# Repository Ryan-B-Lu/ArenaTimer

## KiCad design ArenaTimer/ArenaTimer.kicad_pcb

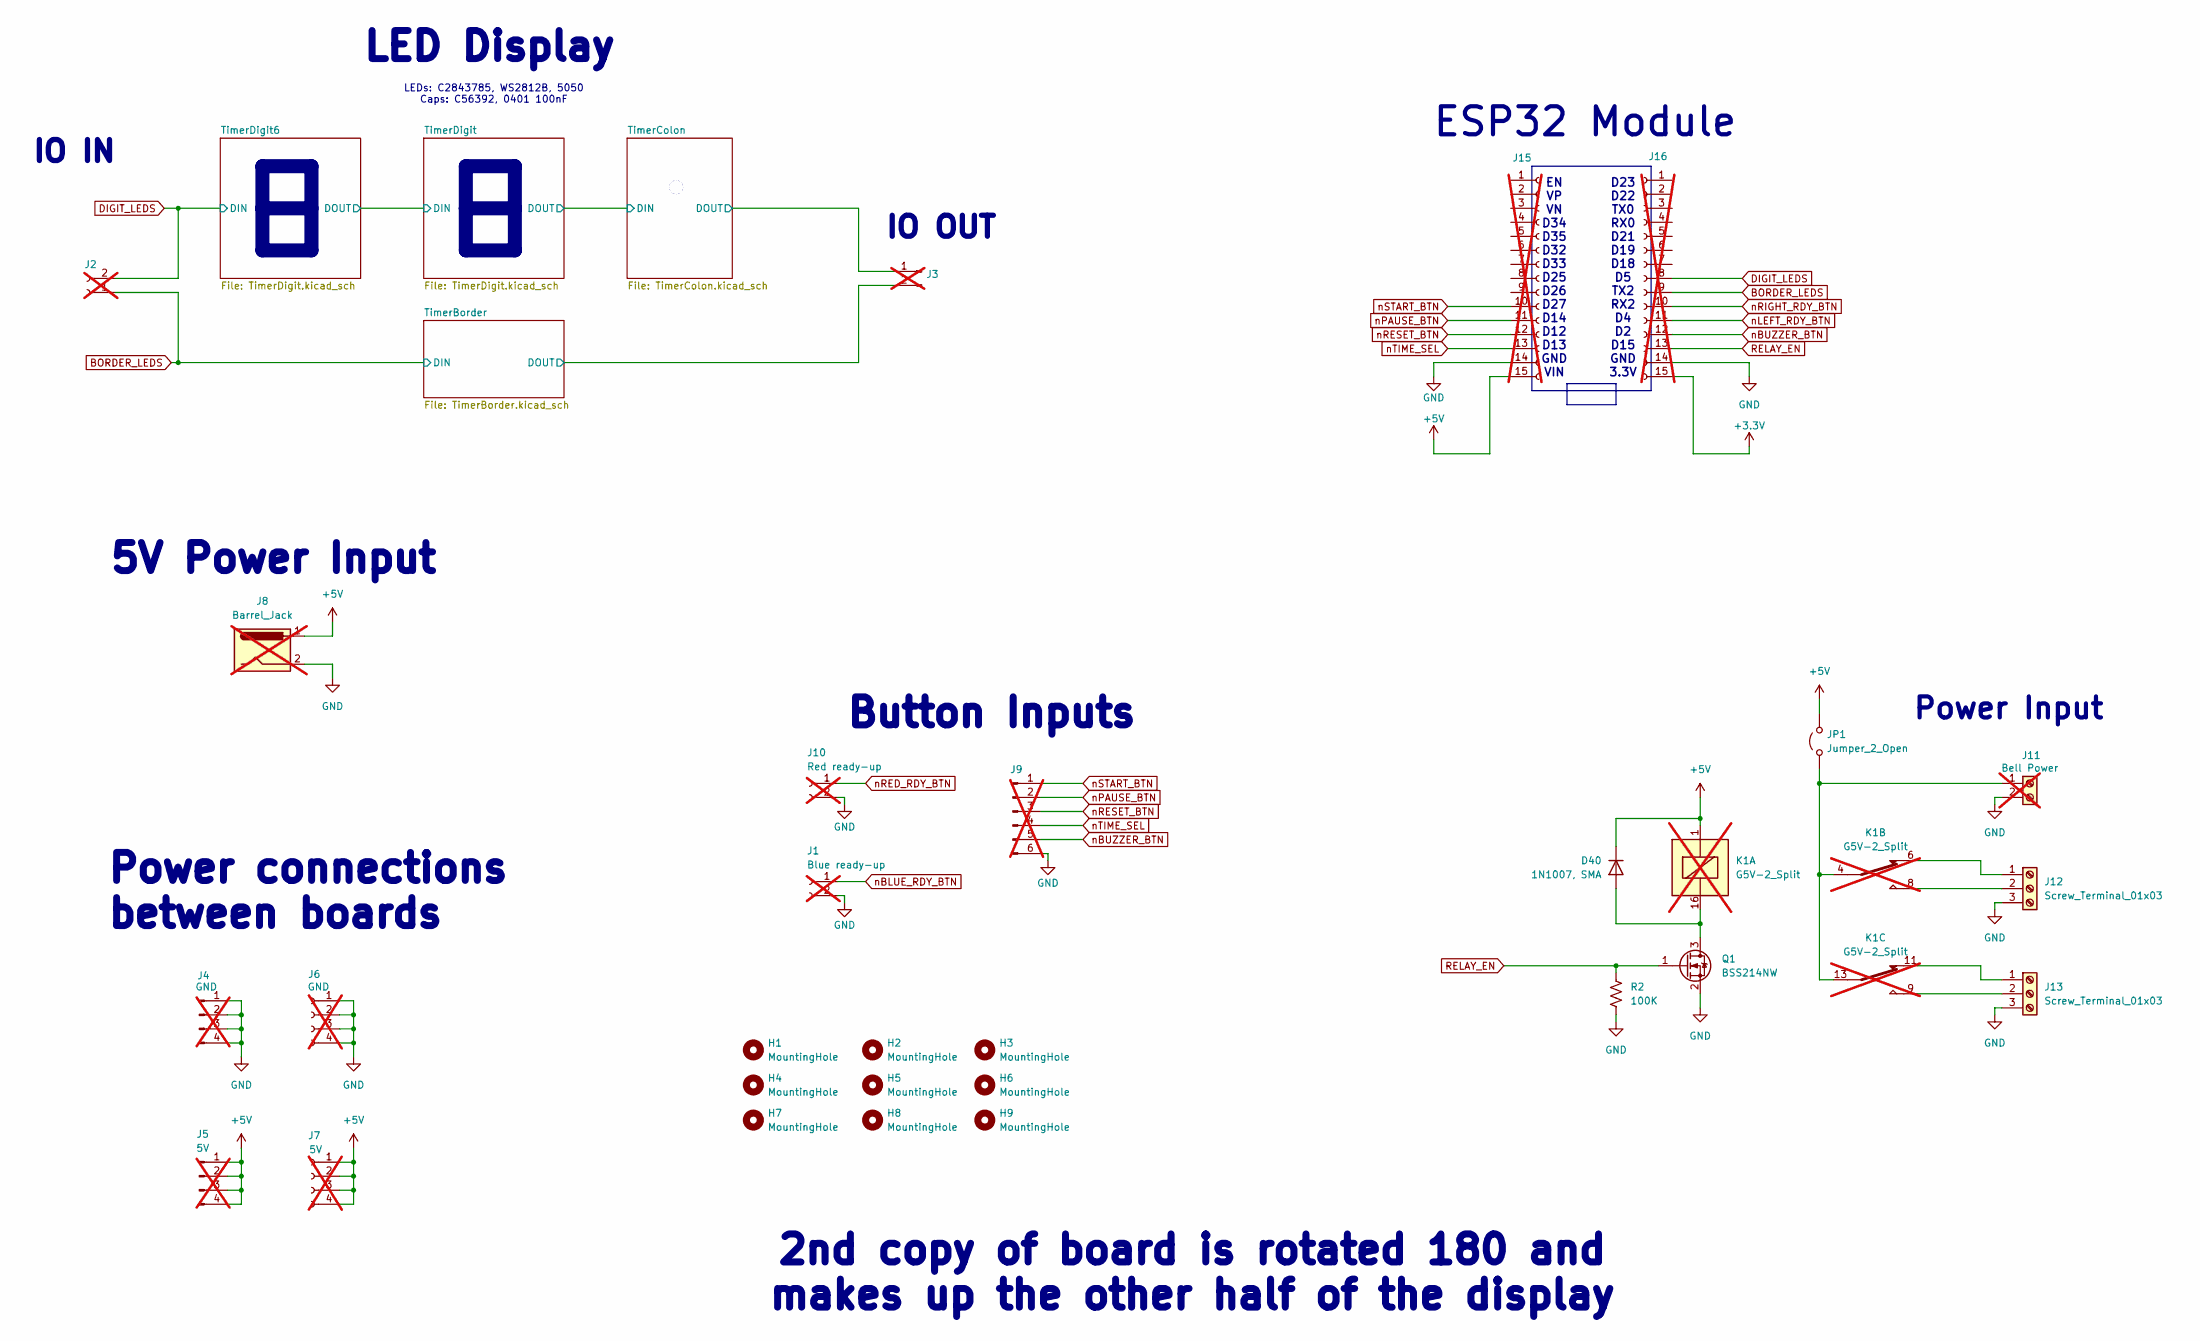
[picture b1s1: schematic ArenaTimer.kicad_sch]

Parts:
D40: 1N1007, SMA; D_SMA; LCSC C727081
H1, H2, H3, H4, H5, H6, H7, H8, H9: MountingHole; MountingHole_3.2mm_M3
J1: Blue ready-up; JST_EH_S2B-EH_1x02_P2.50mm_Horizontal; LCSC C19271377; not fitted
J2: Conn_01x02_Socket; PinSocket_1x02_P2.54mm_Horizontal; not fitted
J3: Conn_01x02_Pin; PinHeader_1x02_P2.54mm_Horizontal; not fitted
J4: GND; PinHeader_1x04_P2.54mm_Horizontal; not fitted
J5: 5V; PinHeader_1x04_P2.54mm_Horizontal; not fitted
J6: GND; PinSocket_1x04_P2.54mm_Horizontal; LCSC C5142237; not fitted
J7: 5V; PinSocket_1x04_P2.54mm_Horizontal; LCSC C5142237; not fitted
J8: Barrel_Jack; BarrelJack_Horizontal; LCSC C381115; not fitted
J9: Conn_01x06_Pin; JST_EH_S6B-EH_1x06_P2.50mm_Horizontal; not fitted
J10: Red ready-up; JST_EH_S2B-EH_1x02_P2.50mm_Horizontal; LCSC C19271377; not fitted
J11: Bell Power; TerminalBlock_bornier-2_P5.08mm; LCSC C5142622; not fitted
J12, J13: Screw_Terminal_01x03; TerminalBlock_bornier-3_P5.08mm
J15, J16: Conn_01x15_Socket; PinSocket_1x15_P2.54mm_Vertical; LCSC C124408; not fitted
JP1: Jumper_2_Open; SolderJumper-2_P1.3mm_Open_RoundedPad1.0x1.5mm
K1: G5V-2_Split; Relay_DPDT_Omron_G5V-2; LCSC C27269; not fitted
Q1: BSS214NW; SOT-323_SC-70; LCSC C412741
R2: 100K; R_0402_1005Metric; LCSC C25530

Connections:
+3.3V: J16.15
+5V: D40.1 (K), J5.1, J5.2, J5.3, J5.4, J7.1, J7.2, J7.3, J7.4, J8.1, J15.15, JP1.2 (B), K1.1; also elsewhere on the board
/TimerBorder/DOUT: J3.2; also elsewhere on the board
/TimerColon/DOUT: J3.1; also elsewhere on the board
BORDER_LEDS: J2.1, J16.9; also elsewhere on the board
DIGIT_LEDS: J2.2, J16.8; also elsewhere on the board
GND: J1.2, J4.1, J4.2, J4.3, J4.4, J6.1, J6.2, J6.3, J6.4, J8.2, J9.6, J10.2, J11.2, J12.3, J13.3, J15.14, J16.14, Q1.2 (S), R2.2; also elsewhere on the board
unnamed: D40.2 (A), K1.16, Q1.3 (D)
unnamed: J11.1, JP1.1 (A), K1.4, K1.13
unnamed: J12.1, K1.6
unnamed: J12.2, K1.8
unnamed: J13.1, K1.11
unnamed: J13.2, K1.9
RELAY_EN: J16.13, Q1.1 (G), R2.1
nBLUE_RDY_BTN: J1.1
nBUZZER_BTN: J9.5, J16.12
nLEFT_RDY_BTN: J16.11
nPAUSE_BTN: J9.2, J15.11
nRED_RDY_BTN: J10.1
nRESET_BTN: J9.3, J15.12
nRIGHT_RDY_BTN: J16.10
nSTART_BTN: J9.1, J15.10
nTIME_SEL: J9.4, J15.13

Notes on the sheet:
EN VP VN D34 D35 D32 D33 D25 D26 D27 D14 D12 D13 GND VIN
IO IN
Power connections between boards
5V Power Input
IO OUT
Power Input
2nd copy of board is rotated 180 and makes up the other half of the display
Button Inputs
D23 D22 TX0 RX0 D21 D19 D18 D5 TX2 RX2 D4 D2 D15 GND 3.3V
LEDs: C2843785, WS2812B, 5050 Caps: C56392, 0401 100nF
ESP32 Module
LED Display

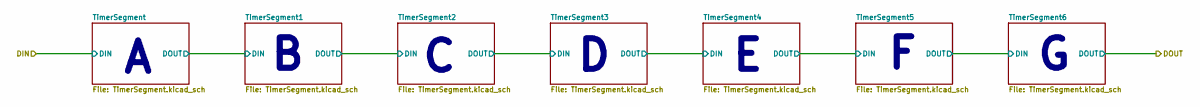
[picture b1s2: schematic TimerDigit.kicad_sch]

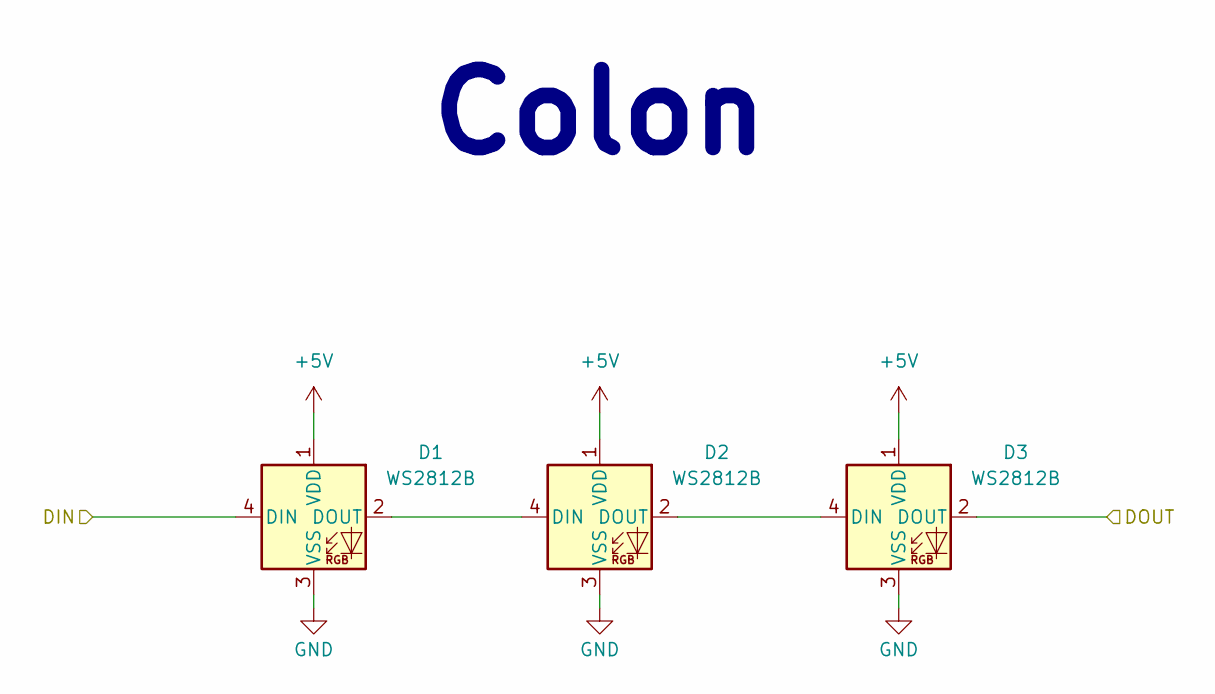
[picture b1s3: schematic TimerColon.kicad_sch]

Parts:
D1, D2, D3: WS2812B; LED_WS2812B_PLCC4_5.0x5.0mm_P3.2mm; LCSC C2843785

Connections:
+5V: D1.1 (VDD), D2.1 (VDD), D3.1 (VDD); also elsewhere on the board
/TimerColon/DIN: D1.4 (DIN); also elsewhere on the board
/TimerColon/DOUT: D3.2 (DOUT); also elsewhere on the board
GND: D1.3 (VSS), D2.3 (VSS), D3.3 (VSS); also elsewhere on the board
unnamed: D1.2 (DOUT), D2.4 (DIN)
unnamed: D2.2 (DOUT), D3.4 (DIN)

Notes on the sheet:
Colon

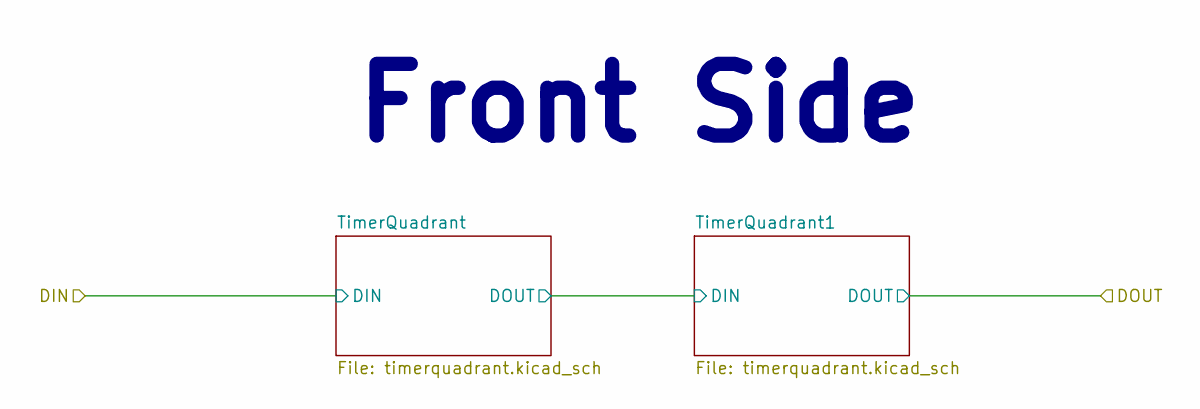
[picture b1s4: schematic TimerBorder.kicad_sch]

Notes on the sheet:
Front Side

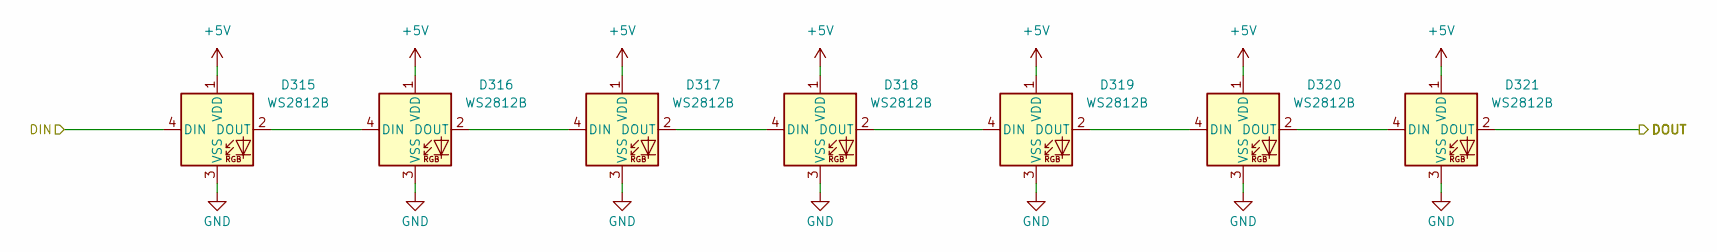
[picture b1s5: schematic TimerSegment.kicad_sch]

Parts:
D315, D316, D317, D318, D319, D320, D321: WS2812B; LED_WS2812B_PLCC4_5.0x5.0mm_P3.2mm; LCSC C2843785

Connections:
+5V: D315.1 (VDD), D316.1 (VDD), D317.1 (VDD), D318.1 (VDD), D319.1 (VDD), D320.1 (VDD), D321.1 (VDD); also elsewhere on the board
/TimerDigit6/TimerSegment5/DOUT: D315.4 (DIN); also elsewhere on the board
/TimerDigit/DIN: D321.2 (DOUT); also elsewhere on the board
GND: D315.3 (VSS), D316.3 (VSS), D317.3 (VSS), D318.3 (VSS), D319.3 (VSS), D320.3 (VSS), D321.3 (VSS); also elsewhere on the board
unnamed: D315.2 (DOUT), D316.4 (DIN)
unnamed: D316.2 (DOUT), D317.4 (DIN)
unnamed: D317.2 (DOUT), D318.4 (DIN)
unnamed: D318.2 (DOUT), D319.4 (DIN)
unnamed: D319.2 (DOUT), D320.4 (DIN)
unnamed: D320.2 (DOUT), D321.4 (DIN)

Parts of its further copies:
D70, D71, D72, D73, D74, D75, D76, D77, D78, D79, D80, D81, D82, D83, D112, D113, D114, D115, D116, D117, D118, D154, D155, D156, D157, D158, D159, D160, D238, D239, D240, D241, D242, D243, D244, D245, D246, D247, D248, D249, D250, D251, D287, D288, D289, D290, D291, D292, D293, D294, D295, D296, D297, D298, D299, D300, D301, D302, D303, D304, D305, D306, D307, D308, D309, D310, D311, D312, D313, D314, D322, D323, D324, D325, D326, D327, D328, D329, D330, D331, D332, D333, D334, D335, D336, D337, D338, D339, D340, D341, D342: WS2812B; LED_WS2812B_PLCC4_5.0x5.0mm_P3.2mm; LCSC C2843785

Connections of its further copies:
+5V: D70.1 (VDD), D71.1 (VDD), D72.1 (VDD), D73.1 (VDD), D74.1 (VDD), D75.1 (VDD), D76.1 (VDD), D77.1 (VDD), D78.1 (VDD), D79.1 (VDD), D80.1 (VDD), D81.1 (VDD), D82.1 (VDD), D83.1 (VDD), D112.1 (VDD), D113.1 (VDD), D114.1 (VDD), D115.1 (VDD), D116.1 (VDD), D117.1 (VDD), D118.1 (VDD), D154.1 (VDD), D155.1 (VDD), D156.1 (VDD), D157.1 (VDD), D158.1 (VDD), D159.1 (VDD), D160.1 (VDD), D238.1 (VDD), D239.1 (VDD), D240.1 (VDD), D241.1 (VDD), D242.1 (VDD), D243.1 (VDD), D244.1 (VDD), D245.1 (VDD), D246.1 (VDD), D247.1 (VDD), D248.1 (VDD), D249.1 (VDD), D250.1 (VDD), D251.1 (VDD), D287.1 (VDD), D288.1 (VDD), D289.1 (VDD), D290.1 (VDD), D291.1 (VDD), D292.1 (VDD), D293.1 (VDD), D294.1 (VDD), D295.1 (VDD), D296.1 (VDD), D297.1 (VDD), D298.1 (VDD), D299.1 (VDD), D300.1 (VDD), D301.1 (VDD), D302.1 (VDD), D303.1 (VDD), D304.1 (VDD), D305.1 (VDD), D306.1 (VDD), D307.1 (VDD), D308.1 (VDD), D309.1 (VDD), D310.1 (VDD), D311.1 (VDD), D312.1 (VDD), D313.1 (VDD), D314.1 (VDD), D322.1 (VDD), D323.1 (VDD), D324.1 (VDD), D325.1 (VDD), D326.1 (VDD), D327.1 (VDD), D328.1 (VDD), D329.1 (VDD), D330.1 (VDD), D331.1 (VDD), D332.1 (VDD), D333.1 (VDD), D334.1 (VDD), D335.1 (VDD), D336.1 (VDD), D337.1 (VDD), D338.1 (VDD), D339.1 (VDD), D340.1 (VDD), D341.1 (VDD), D342.1 (VDD); also elsewhere on the board
/TimerColon/DIN: D293.2 (DOUT); also elsewhere on the board
/TimerDigit6/TimerSegment1/DOUT: D308.4 (DIN), D342.2 (DOUT)
/TimerDigit6/TimerSegment2/DOUT: D301.4 (DIN), D314.2 (DOUT)
/TimerDigit6/TimerSegment3/DOUT: D294.4 (DIN), D307.2 (DOUT)
/TimerDigit6/TimerSegment4/DOUT: D300.2 (DOUT), D322.4 (DIN)
/TimerDigit6/TimerSegment5/DOUT: D328.2 (DOUT); also elsewhere on the board
/TimerDigit6/TimerSegment/DOUT: D335.2 (DOUT), D336.4 (DIN)
/TimerDigit/DIN: D70.4 (DIN); also elsewhere on the board
/TimerDigit/TimerSegment1/DOUT: D83.2 (DOUT), D112.4 (DIN)
/TimerDigit/TimerSegment2/DOUT: D118.2 (DOUT), D154.4 (DIN)
/TimerDigit/TimerSegment3/DOUT: D160.2 (DOUT), D238.4 (DIN)
/TimerDigit/TimerSegment4/DOUT: D244.2 (DOUT), D245.4 (DIN)
/TimerDigit/TimerSegment5/DOUT: D251.2 (DOUT), D287.4 (DIN)
/TimerDigit/TimerSegment/DOUT: D76.2 (DOUT), D77.4 (DIN)
DIGIT_LEDS: D329.4 (DIN); also elsewhere on the board
GND: D70.3 (VSS), D71.3 (VSS), D72.3 (VSS), D73.3 (VSS), D74.3 (VSS), D75.3 (VSS), D76.3 (VSS), D77.3 (VSS), D78.3 (VSS), D79.3 (VSS), D80.3 (VSS), D81.3 (VSS), D82.3 (VSS), D83.3 (VSS), D112.3 (VSS), D113.3 (VSS), D114.3 (VSS), D115.3 (VSS), D116.3 (VSS), D117.3 (VSS), D118.3 (VSS), D154.3 (VSS), D155.3 (VSS), D156.3 (VSS), D157.3 (VSS), D158.3 (VSS), D159.3 (VSS), D160.3 (VSS), D238.3 (VSS), D239.3 (VSS), D240.3 (VSS), D241.3 (VSS), D242.3 (VSS), D243.3 (VSS), D244.3 (VSS), D245.3 (VSS), D246.3 (VSS), D247.3 (VSS), D248.3 (VSS), D249.3 (VSS), D250.3 (VSS), D251.3 (VSS), D287.3 (VSS), D288.3 (VSS), D289.3 (VSS), D290.3 (VSS), D291.3 (VSS), D292.3 (VSS), D293.3 (VSS), D294.3 (VSS), D295.3 (VSS), D296.3 (VSS), D297.3 (VSS), D298.3 (VSS), D299.3 (VSS), D300.3 (VSS), D301.3 (VSS), D302.3 (VSS), D303.3 (VSS), D304.3 (VSS), D305.3 (VSS), D306.3 (VSS), D307.3 (VSS), D308.3 (VSS), D309.3 (VSS), D310.3 (VSS), D311.3 (VSS), D312.3 (VSS), D313.3 (VSS), D314.3 (VSS), D322.3 (VSS), D323.3 (VSS), D324.3 (VSS), D325.3 (VSS), D326.3 (VSS), D327.3 (VSS), D328.3 (VSS), D329.3 (VSS), D330.3 (VSS), D331.3 (VSS), D332.3 (VSS), D333.3 (VSS), D334.3 (VSS), D335.3 (VSS), D336.3 (VSS), D337.3 (VSS), D338.3 (VSS), D339.3 (VSS), D340.3 (VSS), D341.3 (VSS), D342.3 (VSS); also elsewhere on the board
unnamed: D70.2 (DOUT), D71.4 (DIN)
unnamed: D71.2 (DOUT), D72.4 (DIN)
unnamed: D72.2 (DOUT), D73.4 (DIN)
unnamed: D73.2 (DOUT), D74.4 (DIN)
unnamed: D74.2 (DOUT), D75.4 (DIN)
unnamed: D75.2 (DOUT), D76.4 (DIN)
unnamed: D77.2 (DOUT), D78.4 (DIN)
unnamed: D78.2 (DOUT), D79.4 (DIN)
unnamed: D79.2 (DOUT), D80.4 (DIN)
unnamed: D80.2 (DOUT), D81.4 (DIN)
unnamed: D81.2 (DOUT), D82.4 (DIN)
unnamed: D82.2 (DOUT), D83.4 (DIN)
unnamed: D112.2 (DOUT), D113.4 (DIN)
unnamed: D113.2 (DOUT), D114.4 (DIN)
unnamed: D114.2 (DOUT), D115.4 (DIN)
unnamed: D115.2 (DOUT), D116.4 (DIN)
unnamed: D116.2 (DOUT), D117.4 (DIN)
unnamed: D117.2 (DOUT), D118.4 (DIN)
unnamed: D154.2 (DOUT), D155.4 (DIN)
unnamed: D155.2 (DOUT), D156.4 (DIN)
unnamed: D156.2 (DOUT), D157.4 (DIN)
unnamed: D157.2 (DOUT), D158.4 (DIN)
unnamed: D158.2 (DOUT), D159.4 (DIN)
unnamed: D159.2 (DOUT), D160.4 (DIN)
unnamed: D238.2 (DOUT), D239.4 (DIN)
unnamed: D239.2 (DOUT), D240.4 (DIN)
unnamed: D240.2 (DOUT), D241.4 (DIN)
unnamed: D241.2 (DOUT), D242.4 (DIN)
unnamed: D242.2 (DOUT), D243.4 (DIN)
unnamed: D243.2 (DOUT), D244.4 (DIN)
unnamed: D245.2 (DOUT), D246.4 (DIN)
unnamed: D246.2 (DOUT), D247.4 (DIN)
unnamed: D247.2 (DOUT), D248.4 (DIN)
unnamed: D248.2 (DOUT), D249.4 (DIN)
unnamed: D249.2 (DOUT), D250.4 (DIN)
unnamed: D250.2 (DOUT), D251.4 (DIN)
unnamed: D287.2 (DOUT), D288.4 (DIN)
unnamed: D288.2 (DOUT), D289.4 (DIN)
unnamed: D289.2 (DOUT), D290.4 (DIN)
unnamed: D290.2 (DOUT), D291.4 (DIN)
unnamed: D291.2 (DOUT), D292.4 (DIN)
unnamed: D292.2 (DOUT), D293.4 (DIN)
unnamed: D294.2 (DOUT), D295.4 (DIN)
unnamed: D295.2 (DOUT), D296.4 (DIN)
unnamed: D296.2 (DOUT), D297.4 (DIN)
unnamed: D297.2 (DOUT), D298.4 (DIN)
unnamed: D298.2 (DOUT), D299.4 (DIN)
unnamed: D299.2 (DOUT), D300.4 (DIN)
unnamed: D301.2 (DOUT), D302.4 (DIN)
unnamed: D302.2 (DOUT), D303.4 (DIN)
unnamed: D303.2 (DOUT), D304.4 (DIN)
unnamed: D304.2 (DOUT), D305.4 (DIN)
unnamed: D305.2 (DOUT), D306.4 (DIN)
unnamed: D306.2 (DOUT), D307.4 (DIN)
unnamed: D308.2 (DOUT), D309.4 (DIN)
unnamed: D309.2 (DOUT), D310.4 (DIN)
unnamed: D310.2 (DOUT), D311.4 (DIN)
unnamed: D311.2 (DOUT), D312.4 (DIN)
unnamed: D312.2 (DOUT), D313.4 (DIN)
unnamed: D313.2 (DOUT), D314.4 (DIN)
unnamed: D322.2 (DOUT), D323.4 (DIN)
unnamed: D323.2 (DOUT), D324.4 (DIN)
unnamed: D324.2 (DOUT), D325.4 (DIN)
unnamed: D325.2 (DOUT), D326.4 (DIN)
unnamed: D326.2 (DOUT), D327.4 (DIN)
unnamed: D327.2 (DOUT), D328.4 (DIN)
unnamed: D329.2 (DOUT), D330.4 (DIN)
unnamed: D330.2 (DOUT), D331.4 (DIN)
unnamed: D331.2 (DOUT), D332.4 (DIN)
unnamed: D332.2 (DOUT), D333.4 (DIN)
unnamed: D333.2 (DOUT), D334.4 (DIN)
unnamed: D334.2 (DOUT), D335.4 (DIN)
unnamed: D336.2 (DOUT), D337.4 (DIN)
unnamed: D337.2 (DOUT), D338.4 (DIN)
unnamed: D338.2 (DOUT), D339.4 (DIN)
unnamed: D339.2 (DOUT), D340.4 (DIN)
unnamed: D340.2 (DOUT), D341.4 (DIN)
unnamed: D341.2 (DOUT), D342.4 (DIN)

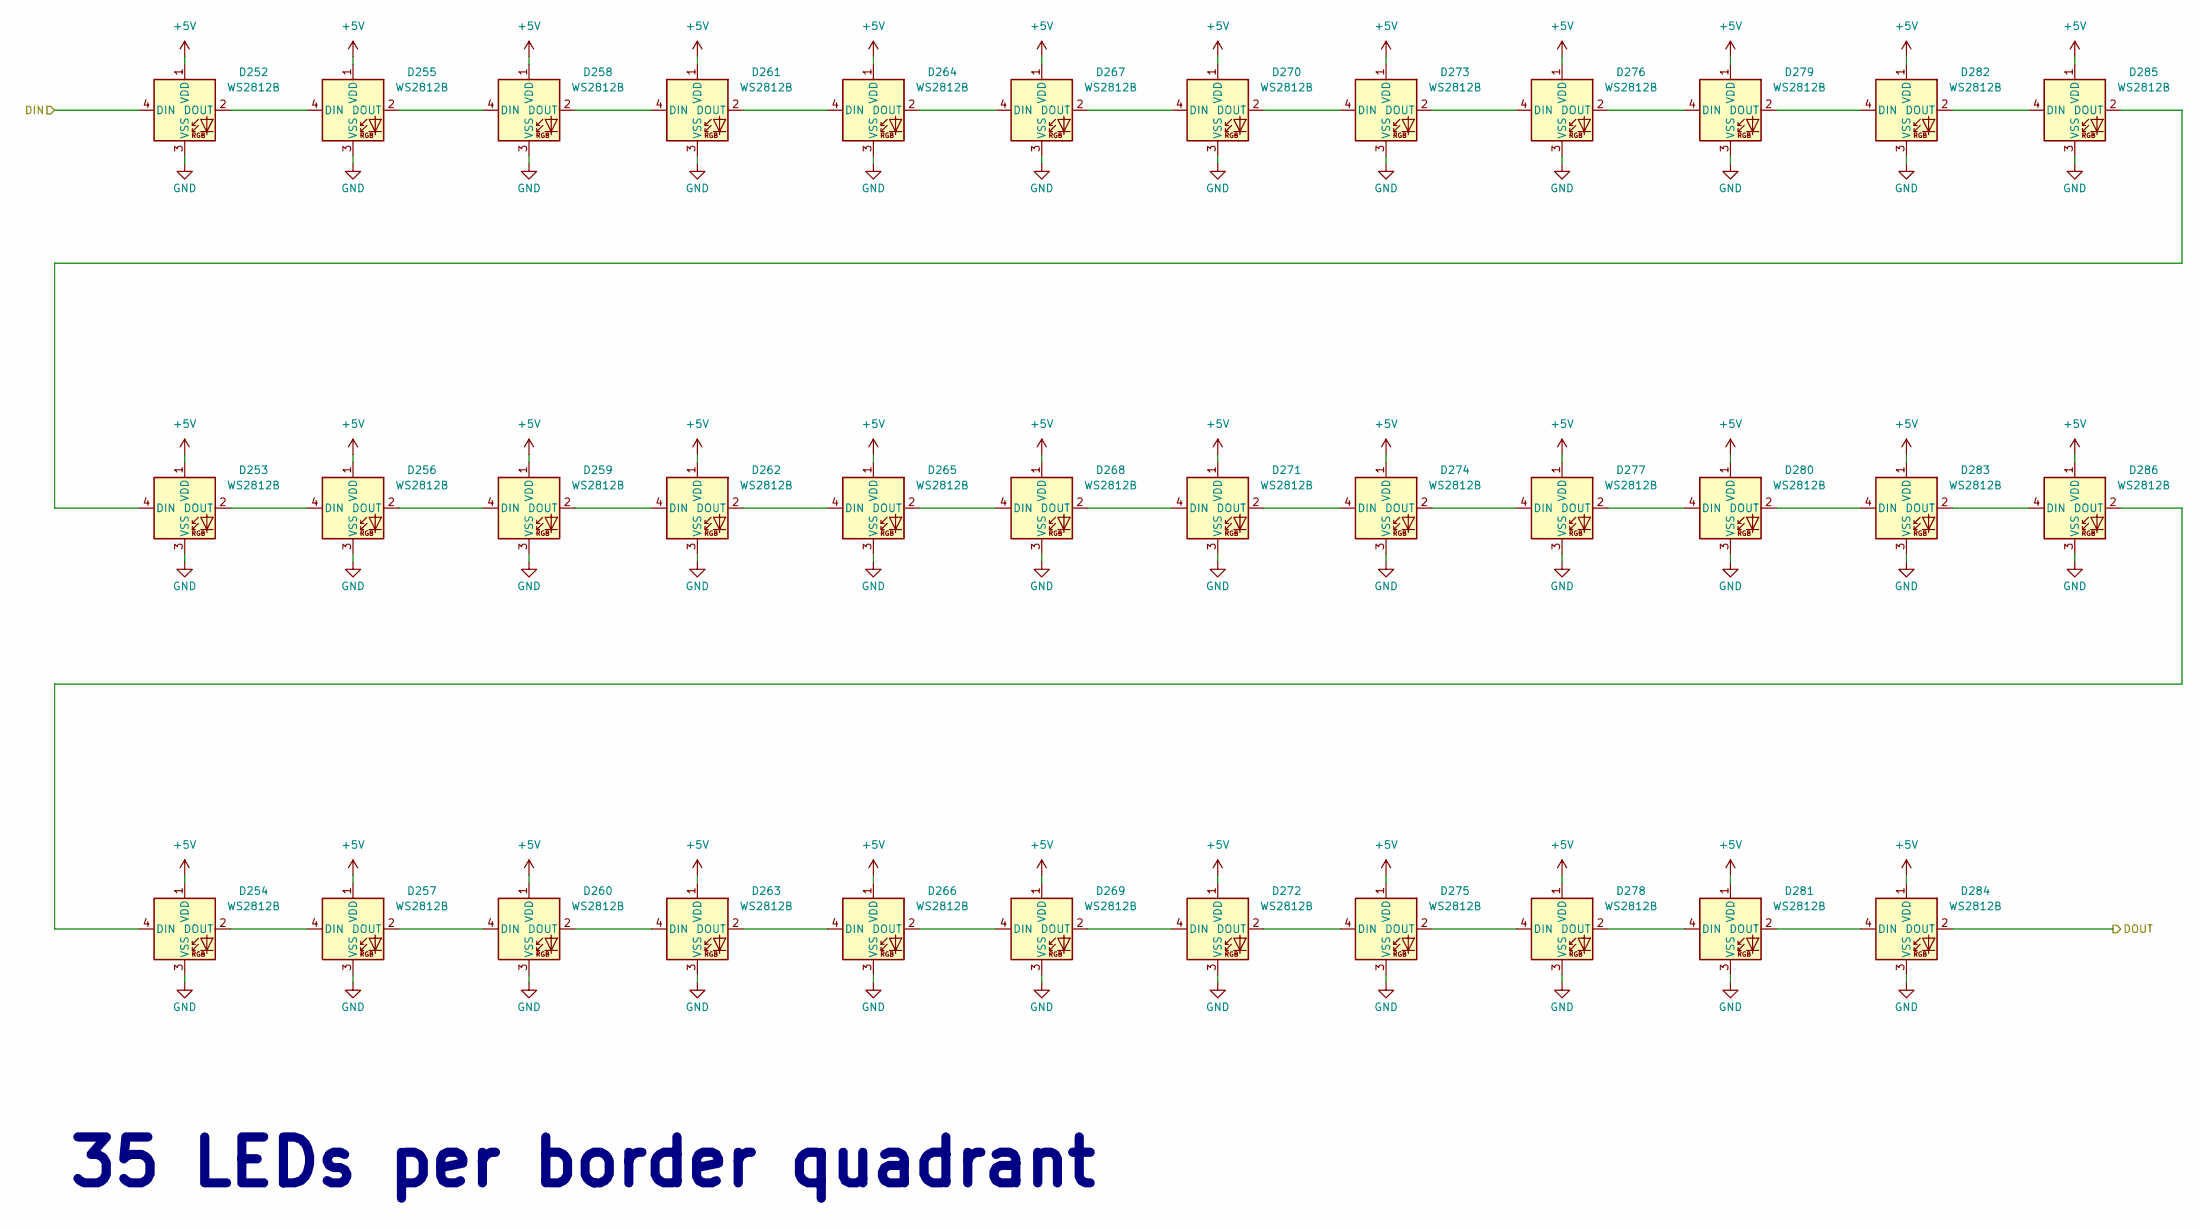
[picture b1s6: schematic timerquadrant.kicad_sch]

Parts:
D252, D253, D254, D255, D256, D257, D258, D259, D260, D261, D262, D263, D264, D265, D266, D267, D268, D269, D270, D271, D272, D273, D274, D275, D276, D277, D278, D279, D280, D281, D282, D283, D284, D285, D286: WS2812B; LED_WS2812B_PLCC4_5.0x5.0mm_P3.2mm; LCSC C2843785

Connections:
+5V: D252.1 (VDD), D253.1 (VDD), D254.1 (VDD), D255.1 (VDD), D256.1 (VDD), D257.1 (VDD), D258.1 (VDD), D259.1 (VDD), D260.1 (VDD), D261.1 (VDD), D262.1 (VDD), D263.1 (VDD), D264.1 (VDD), D265.1 (VDD), D266.1 (VDD), D267.1 (VDD), D268.1 (VDD), D269.1 (VDD), D270.1 (VDD), D271.1 (VDD), D272.1 (VDD), D273.1 (VDD), D274.1 (VDD), D275.1 (VDD), D276.1 (VDD), D277.1 (VDD), D278.1 (VDD), D279.1 (VDD), D280.1 (VDD), D281.1 (VDD), D282.1 (VDD), D283.1 (VDD), D284.1 (VDD), D285.1 (VDD), D286.1 (VDD); also elsewhere on the board
/TimerBorder/TimerQuadrant/DOUT: D284.2 (DOUT); also elsewhere on the board
BORDER_LEDS: D252.4 (DIN); also elsewhere on the board
GND: D252.3 (VSS), D253.3 (VSS), D254.3 (VSS), D255.3 (VSS), D256.3 (VSS), D257.3 (VSS), D258.3 (VSS), D259.3 (VSS), D260.3 (VSS), D261.3 (VSS), D262.3 (VSS), D263.3 (VSS), D264.3 (VSS), D265.3 (VSS), D266.3 (VSS), D267.3 (VSS), D268.3 (VSS), D269.3 (VSS), D270.3 (VSS), D271.3 (VSS), D272.3 (VSS), D273.3 (VSS), D274.3 (VSS), D275.3 (VSS), D276.3 (VSS), D277.3 (VSS), D278.3 (VSS), D279.3 (VSS), D280.3 (VSS), D281.3 (VSS), D282.3 (VSS), D283.3 (VSS), D284.3 (VSS), D285.3 (VSS), D286.3 (VSS); also elsewhere on the board
unnamed: D252.2 (DOUT), D255.4 (DIN)
unnamed: D253.4 (DIN), D285.2 (DOUT)
unnamed: D253.2 (DOUT), D256.4 (DIN)
unnamed: D254.4 (DIN), D286.2 (DOUT)
unnamed: D254.2 (DOUT), D257.4 (DIN)
unnamed: D255.2 (DOUT), D258.4 (DIN)
unnamed: D256.2 (DOUT), D259.4 (DIN)
unnamed: D257.2 (DOUT), D260.4 (DIN)
unnamed: D258.2 (DOUT), D261.4 (DIN)
unnamed: D259.2 (DOUT), D262.4 (DIN)
unnamed: D260.2 (DOUT), D263.4 (DIN)
unnamed: D261.2 (DOUT), D264.4 (DIN)
unnamed: D262.2 (DOUT), D265.4 (DIN)
unnamed: D263.2 (DOUT), D266.4 (DIN)
unnamed: D264.2 (DOUT), D267.4 (DIN)
unnamed: D265.2 (DOUT), D268.4 (DIN)
unnamed: D266.2 (DOUT), D269.4 (DIN)
unnamed: D267.2 (DOUT), D270.4 (DIN)
unnamed: D268.2 (DOUT), D271.4 (DIN)
unnamed: D269.2 (DOUT), D272.4 (DIN)
unnamed: D270.2 (DOUT), D273.4 (DIN)
unnamed: D271.2 (DOUT), D274.4 (DIN)
unnamed: D272.2 (DOUT), D275.4 (DIN)
unnamed: D273.2 (DOUT), D276.4 (DIN)
unnamed: D274.2 (DOUT), D277.4 (DIN)
unnamed: D275.2 (DOUT), D278.4 (DIN)
unnamed: D276.2 (DOUT), D279.4 (DIN)
unnamed: D277.2 (DOUT), D280.4 (DIN)
unnamed: D278.2 (DOUT), D281.4 (DIN)
unnamed: D279.2 (DOUT), D282.4 (DIN)
unnamed: D280.2 (DOUT), D283.4 (DIN)
unnamed: D281.2 (DOUT), D284.4 (DIN)
unnamed: D282.2 (DOUT), D285.4 (DIN)
unnamed: D283.2 (DOUT), D286.4 (DIN)

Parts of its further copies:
D4, D5, D6, D7, D8, D9, D10, D11, D12, D13, D14, D15, D16, D17, D18, D19, D20, D21, D22, D23, D24, D25, D26, D27, D28, D29, D30, D31, D32, D33, D34, D35, D36, D37, D38: WS2812B; LED_WS2812B_PLCC4_5.0x5.0mm_P3.2mm; LCSC C2843785

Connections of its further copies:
+5V: D4.1 (VDD), D5.1 (VDD), D6.1 (VDD), D7.1 (VDD), D8.1 (VDD), D9.1 (VDD), D10.1 (VDD), D11.1 (VDD), D12.1 (VDD), D13.1 (VDD), D14.1 (VDD), D15.1 (VDD), D16.1 (VDD), D17.1 (VDD), D18.1 (VDD), D19.1 (VDD), D20.1 (VDD), D21.1 (VDD), D22.1 (VDD), D23.1 (VDD), D24.1 (VDD), D25.1 (VDD), D26.1 (VDD), D27.1 (VDD), D28.1 (VDD), D29.1 (VDD), D30.1 (VDD), D31.1 (VDD), D32.1 (VDD), D33.1 (VDD), D34.1 (VDD), D35.1 (VDD), D36.1 (VDD), D37.1 (VDD), D38.1 (VDD); also elsewhere on the board
/TimerBorder/DOUT: D36.2 (DOUT); also elsewhere on the board
/TimerBorder/TimerQuadrant/DOUT: D4.4 (DIN); also elsewhere on the board
GND: D4.3 (VSS), D5.3 (VSS), D6.3 (VSS), D7.3 (VSS), D8.3 (VSS), D9.3 (VSS), D10.3 (VSS), D11.3 (VSS), D12.3 (VSS), D13.3 (VSS), D14.3 (VSS), D15.3 (VSS), D16.3 (VSS), D17.3 (VSS), D18.3 (VSS), D19.3 (VSS), D20.3 (VSS), D21.3 (VSS), D22.3 (VSS), D23.3 (VSS), D24.3 (VSS), D25.3 (VSS), D26.3 (VSS), D27.3 (VSS), D28.3 (VSS), D29.3 (VSS), D30.3 (VSS), D31.3 (VSS), D32.3 (VSS), D33.3 (VSS), D34.3 (VSS), D35.3 (VSS), D36.3 (VSS), D37.3 (VSS), D38.3 (VSS); also elsewhere on the board
unnamed: D4.2 (DOUT), D7.4 (DIN)
unnamed: D5.2 (DOUT), D8.4 (DIN)
unnamed: D6.2 (DOUT), D9.4 (DIN)
unnamed: D7.2 (DOUT), D10.4 (DIN)
unnamed: D10.2 (DOUT), D13.4 (DIN)
unnamed: D8.2 (DOUT), D11.4 (DIN)
unnamed: D11.2 (DOUT), D14.4 (DIN)
unnamed: D9.2 (DOUT), D12.4 (DIN)
unnamed: D12.2 (DOUT), D15.4 (DIN)
unnamed: D13.2 (DOUT), D16.4 (DIN)
unnamed: D14.2 (DOUT), D17.4 (DIN)
unnamed: D15.2 (DOUT), D18.4 (DIN)
unnamed: D16.2 (DOUT), D19.4 (DIN)
unnamed: D17.2 (DOUT), D20.4 (DIN)
unnamed: D18.2 (DOUT), D21.4 (DIN)
unnamed: D19.2 (DOUT), D22.4 (DIN)
unnamed: D20.2 (DOUT), D23.4 (DIN)
unnamed: D21.2 (DOUT), D24.4 (DIN)
unnamed: D22.2 (DOUT), D25.4 (DIN)
unnamed: D23.2 (DOUT), D26.4 (DIN)
unnamed: D24.2 (DOUT), D27.4 (DIN)
unnamed: D25.2 (DOUT), D28.4 (DIN)
unnamed: D26.2 (DOUT), D29.4 (DIN)
unnamed: D27.2 (DOUT), D30.4 (DIN)
unnamed: D28.2 (DOUT), D31.4 (DIN)
unnamed: D29.2 (DOUT), D32.4 (DIN)
unnamed: D30.2 (DOUT), D33.4 (DIN)
unnamed: D31.2 (DOUT), D34.4 (DIN)
unnamed: D32.2 (DOUT), D35.4 (DIN)
unnamed: D33.2 (DOUT), D36.4 (DIN)
unnamed: D34.2 (DOUT), D37.4 (DIN)
unnamed: D35.2 (DOUT), D38.4 (DIN)
unnamed: D5.4 (DIN), D37.2 (DOUT)
unnamed: D6.4 (DIN), D38.2 (DOUT)

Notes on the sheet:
35 LEDs per border quadrant

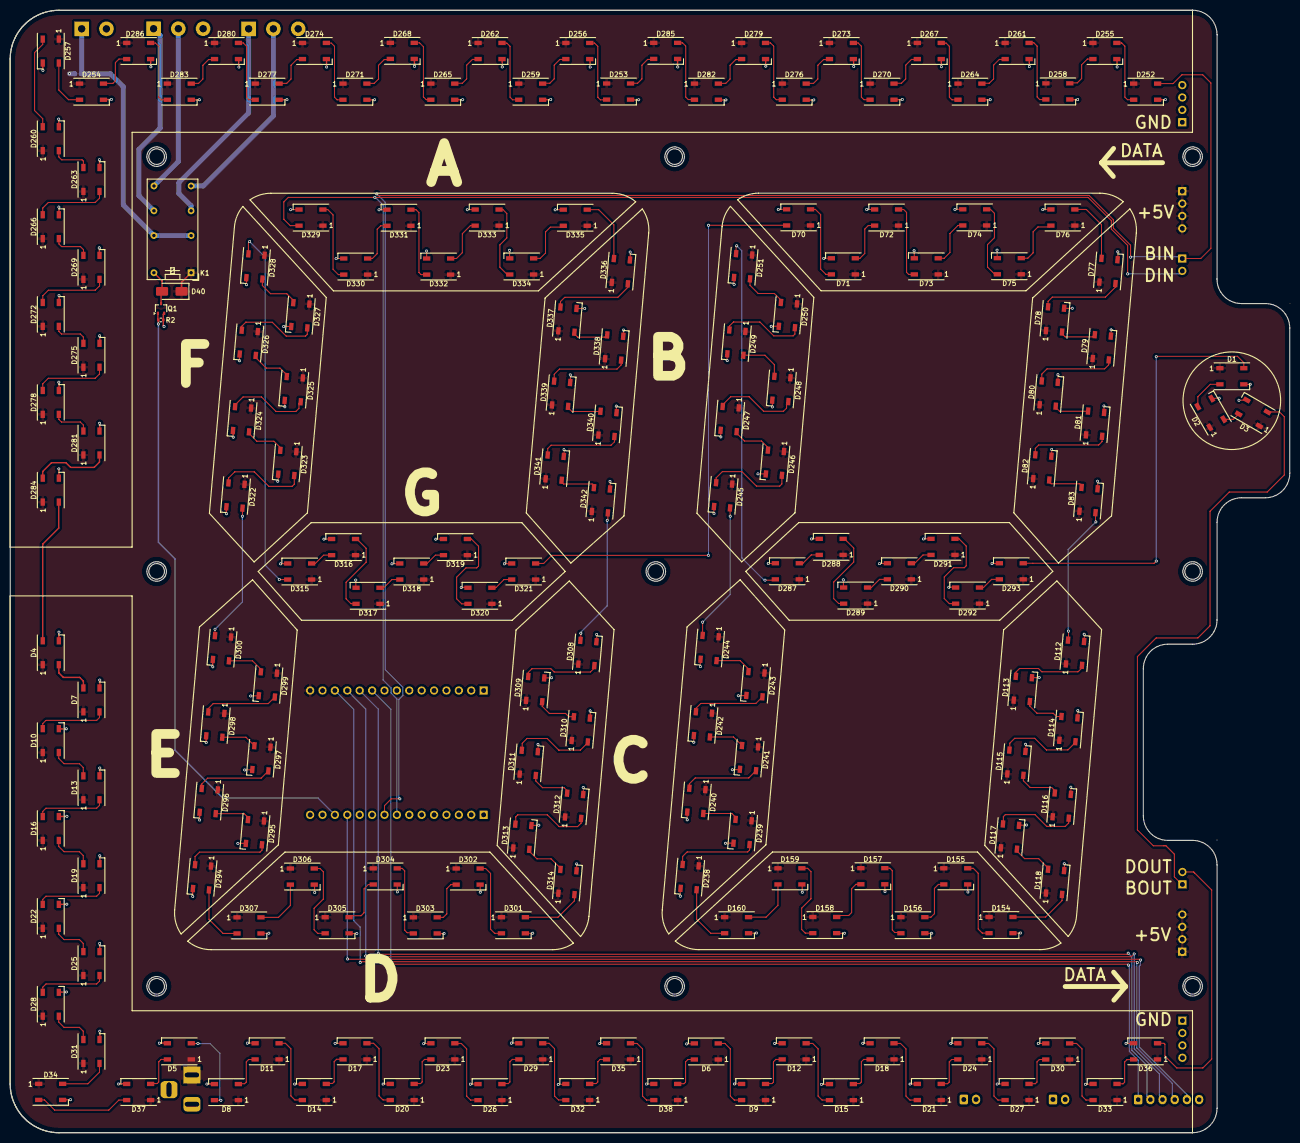
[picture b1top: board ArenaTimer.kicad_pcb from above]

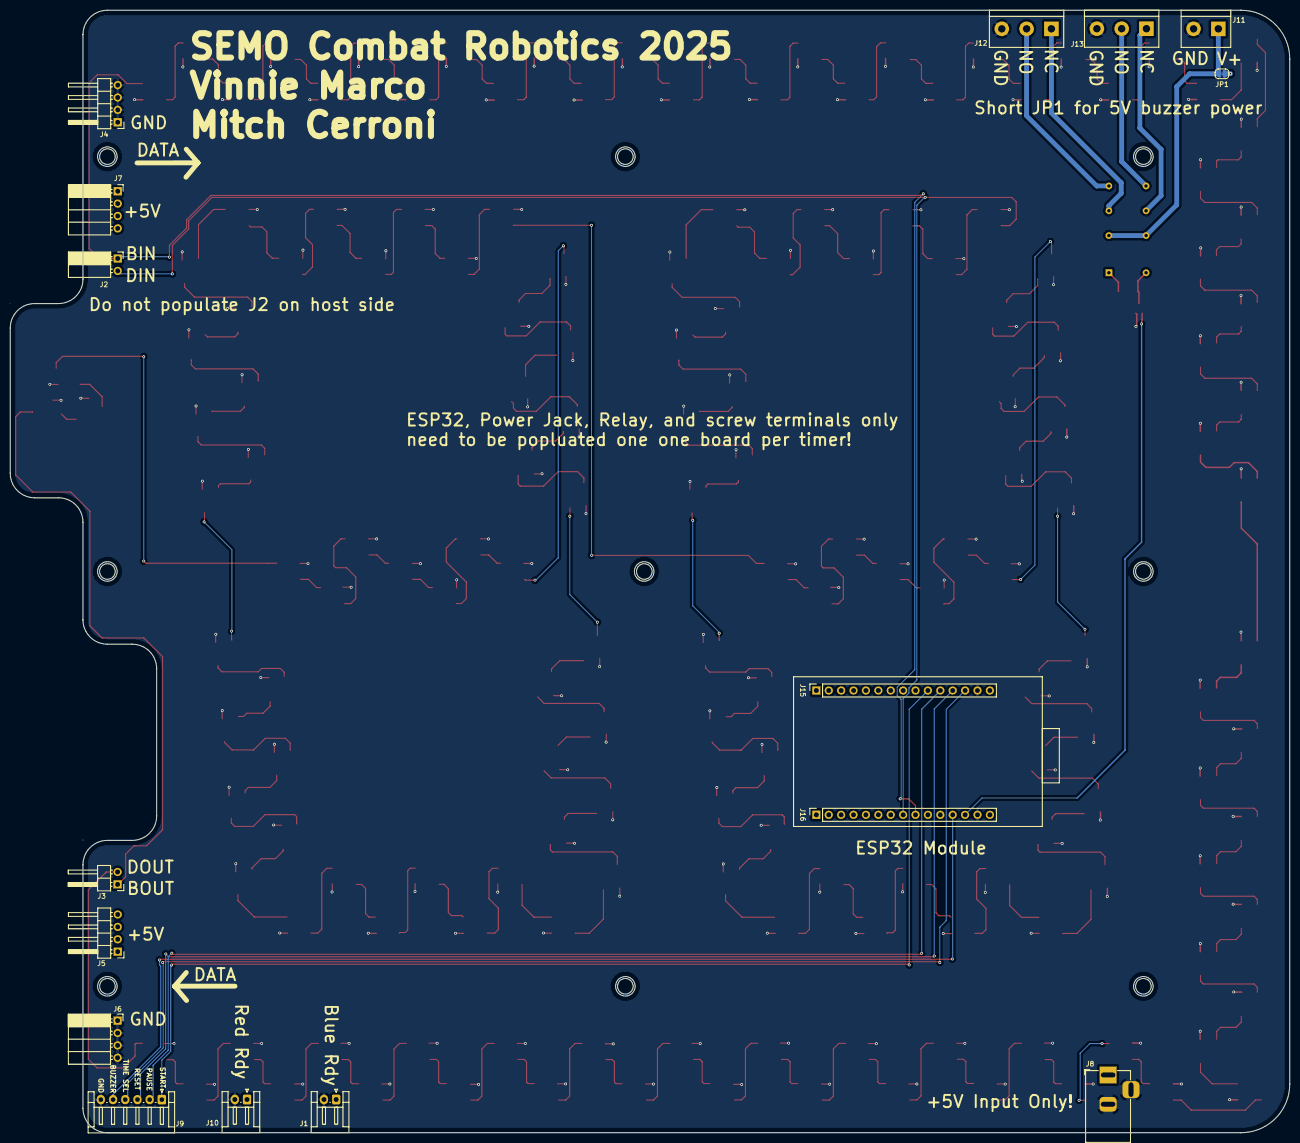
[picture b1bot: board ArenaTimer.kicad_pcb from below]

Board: 2 copper layers, 262.2 x 230.0 mm, 200 parts (16 on the bottom side), 187 nets.

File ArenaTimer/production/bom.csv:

Designator,Footprint,Quantity,Value,LCSC Part #
"D1, D10, D11, D112, D113, D114, D115, D116, D117, D118, D12, D13, D14, D15, D154, D155, D156, D157, D158, D159, D16, D160, D17, D18, D19, D2, D20, D21, D22, D23, D238, D239, D24, D240, D241, D242, D243, D244, D245, D246, D247, D248, D249, D25, D250, D251, D252, D253, D254, D255, D256, D257, D258, D259, D26, D260, D261, D262, D263, D264, D265, D266, D267, D268, D269, D27, D270, D271, D272, D273, D274, D275, D276, D277, D278, D279, D28, D280, D281, D282, D283, D284, D285, D286, D287, D288, D289, D29, D290, D291, D292, D293, D294, D295, D296, D297, D298, D299, D3, D30, D300, D301, D302, D303, D304, D305, D306, D307, D308, D309, D31, D310, D311, D312, D313, D314, D315, D316, D317, D318, D319, D32, D320, D321, D322, D323, D324, D325, D326, D327, D328, D329, D33, D330, D331, D332, D333, D334, D335, D336, D337, D338, D339, D34, D340, D341, D342, D35, D36, D37, D38, D4, D5, D6, D7, D70, D71, D72, D73, D74, D75, D76, D77, D78, D79, D8, D80, D81, D82, D83, D9",LED_WS2812B_PLCC4_5.0x5.0mm_P3.2mm,171,WS2812B,C2843785
